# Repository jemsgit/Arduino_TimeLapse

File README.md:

Arduino_TimeLapse
=================

Timelapse timer on Atmega8L

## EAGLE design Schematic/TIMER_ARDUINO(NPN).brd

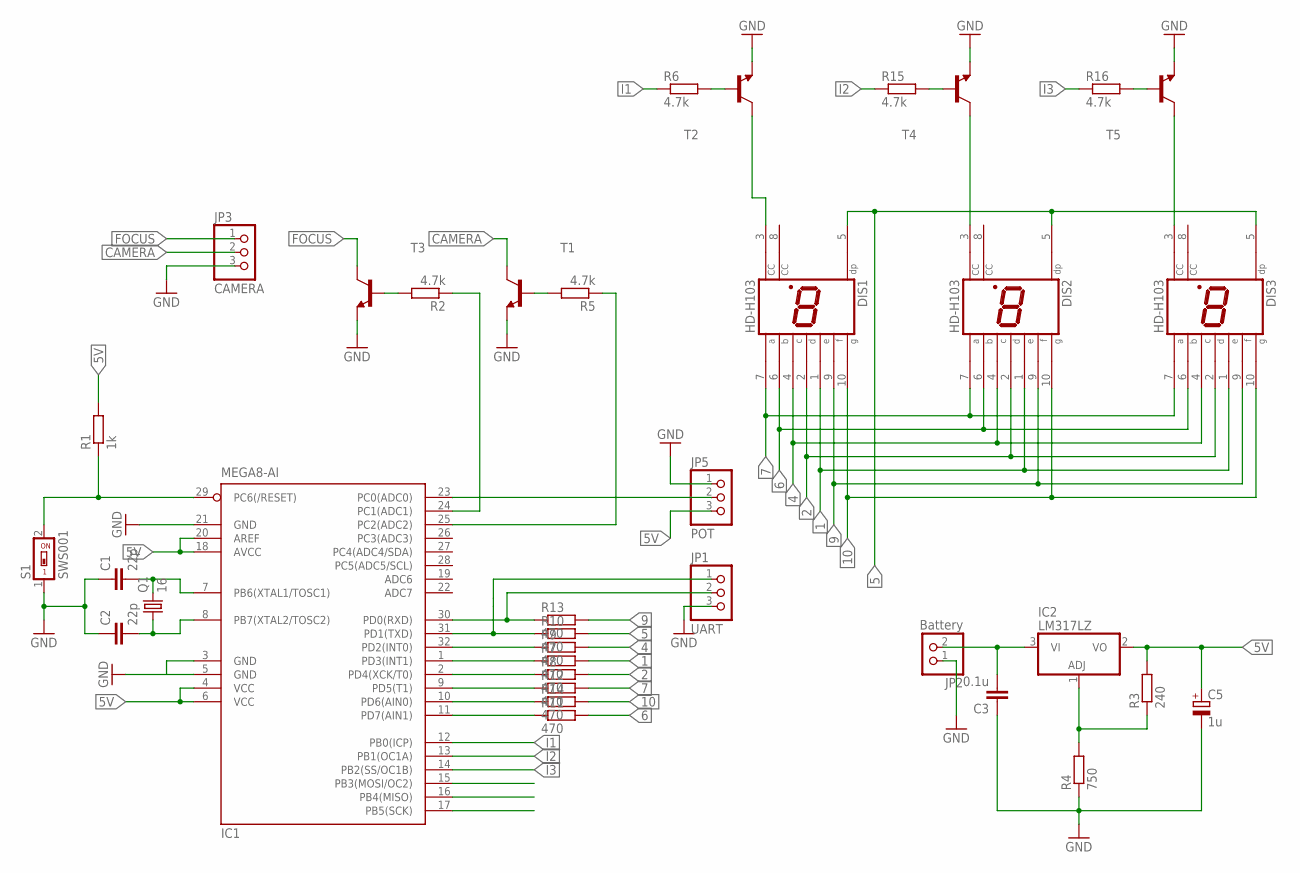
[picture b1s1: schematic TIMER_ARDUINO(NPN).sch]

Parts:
C1, C2: 22p; C0805
C3: 0.1u; C0805
C5: 1u; 153CLV-0405
DIS1, DIS2, DIS3: HD-H103; HDSP-M
IC1: MEGA8-AI; TQFP32-08
IC2: LM317LZ; TO92
JP1: UART; 1X03
JP2: Battery; 1X02
JP3: CAMERA; 1X03
JP5: POT; 1X03
Q1: 16; HC33U-V
R1: 1k; R1206
R2, R5, R6, R15, R16: 4.7k; R0805
R3: 240; R0805
R4: 750; R0805
R7, R8, R9, R10, R11, R12, R13, R14: 470; R0805
S1: SWS001; SMS-001
T1, T2, T3, T4, T5: BC846B-NPN-SOT23-BEC; SOT23-BEC

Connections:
1: DIS1.1 (E), DIS2.1 (E), DIS3.1 (E), R7.2
2: DIS1.2 (D), DIS2.2 (D), DIS3.2 (D), R8.2
4: DIS1.4 (C), DIS2.4 (C), DIS3.4 (C), R9.2
5: DIS1.5 (DP), DIS2.5 (DP), DIS3.5 (DP), R10.2
5V: C5.+, IC1.4 (VCC), IC1.6 (VCC), IC1.18 (AVCC), IC1.20 (AREF), IC2.2 (VO), JP5.3, R1.2, R3.2
6: DIS1.6 (B), DIS2.6 (B), DIS3.6 (B), R11.2
7: DIS1.7 (A), DIS2.7 (A), DIS3.7 (A), R12.2
9: DIS1.9 (F), DIS2.9 (F), DIS3.9 (F), R13.2
10: DIS1.10 (G), DIS2.10 (G), DIS3.10 (G), R14.2
CAMERA: JP3.2, T1.C
FOCUS: JP3.1, T3.C
GND: C1.1, C2.1, C3.1, C5.-, IC1.5 (GND), IC1.21 (GND), JP1.3, JP2.1, JP3.3, JP5.1, R4.1, S1.1, T1.E, T2.E, T3.E, T4.E, T5.E
I1: IC1.12 (PB0(ICP)), R6.1
I2: IC1.13 (PB1(OC1A)), R15.1
I3: IC1.14 (PB2(SS/OC1B)), R16.1
unnamed: IC1.29 (PC6(/RESET)), R1.1, S1.2
unnamed: IC1.23 (PC0(ADC0)), JP5.2
unnamed: IC1.30 (PD0(RXD)), JP1.2, R13.1
unnamed: IC1.31 (PD1(TXD)), JP1.1, R10.1
unnamed: C1.2, IC1.7 (PB6(XTAL1/TOSC1)), Q1.2
unnamed: IC1.32 (PD2(INT0)), R9.1
unnamed: C2.2, IC1.8 (PB7(XTAL2/TOSC2)), Q1.1
unnamed: IC1.1 (PD3(INT1)), R7.1
unnamed: IC1.2 (PD4(XCK/T0)), R8.1
unnamed: IC1.9 (PD5(T1)), R12.1
unnamed: IC1.10 (PD6(AIN0)), R14.1
unnamed: IC1.11 (PD7(AIN1)), R11.1
unnamed: R2.2, T3.B
unnamed: C3.2, IC2.3 (VI), JP2.2
unnamed: IC2.1 (ADJ), R3.1, R4.2
unnamed: IC1.24 (PC1(ADC1)), R2.1
unnamed: R5.2, T1.B
unnamed: IC1.25 (PC2(ADC2)), R5.1
unnamed: R6.2, T2.B
unnamed: R15.2, T4.B
unnamed: R16.2, T5.B
unnamed: DIS1.3 (CC), T2.C
unnamed: DIS2.3 (CC), T4.C
unnamed: DIS3.3 (CC), T5.C

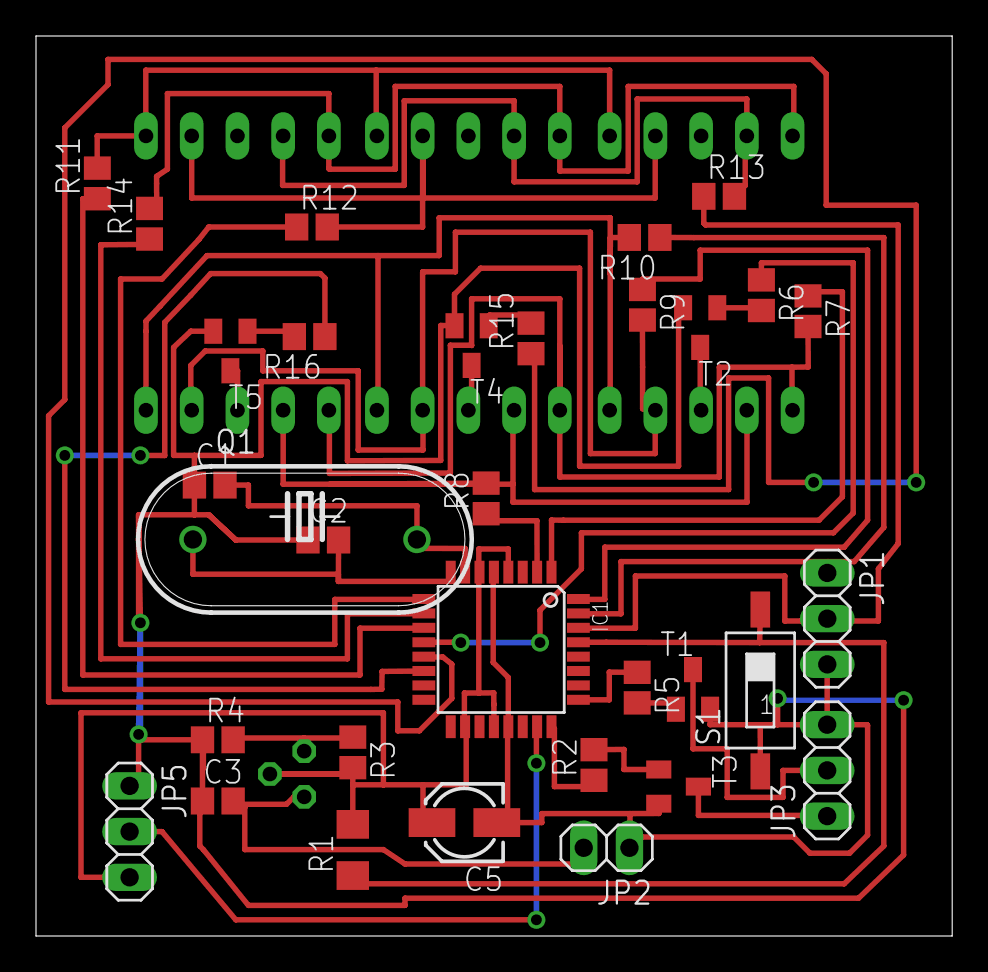
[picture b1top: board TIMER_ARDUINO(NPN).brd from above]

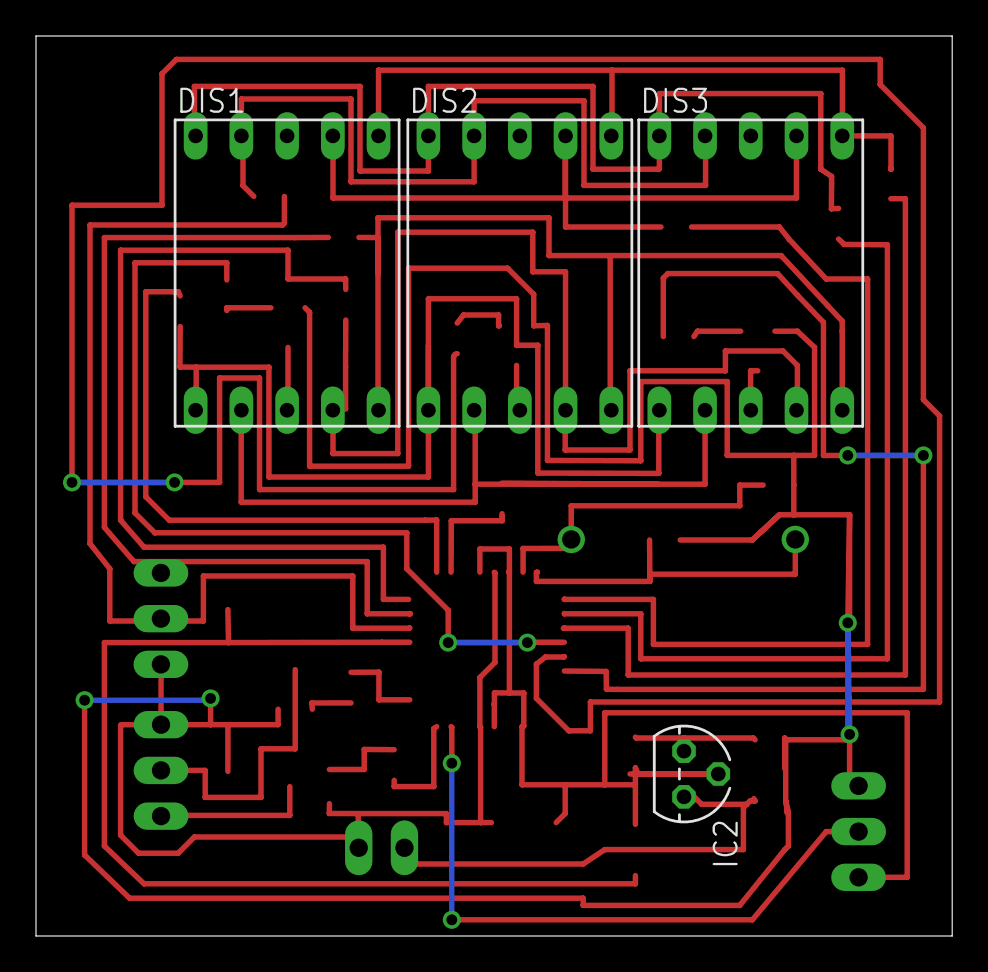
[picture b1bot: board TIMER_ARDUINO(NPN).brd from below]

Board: 2 copper layers, 50.9 x 50.0 mm, 36 parts (4 on the bottom side), 39 nets.

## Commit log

2013-11-30 Add schematic files and code
2013-11-30 Add bootloader fos ATmega8L
2013-11-30 sorted
2013-11-30 Create gh-pages branch via GitHub
2013-11-30 clean
2013-11-30 clean2
2013-12-02 add correct soft
